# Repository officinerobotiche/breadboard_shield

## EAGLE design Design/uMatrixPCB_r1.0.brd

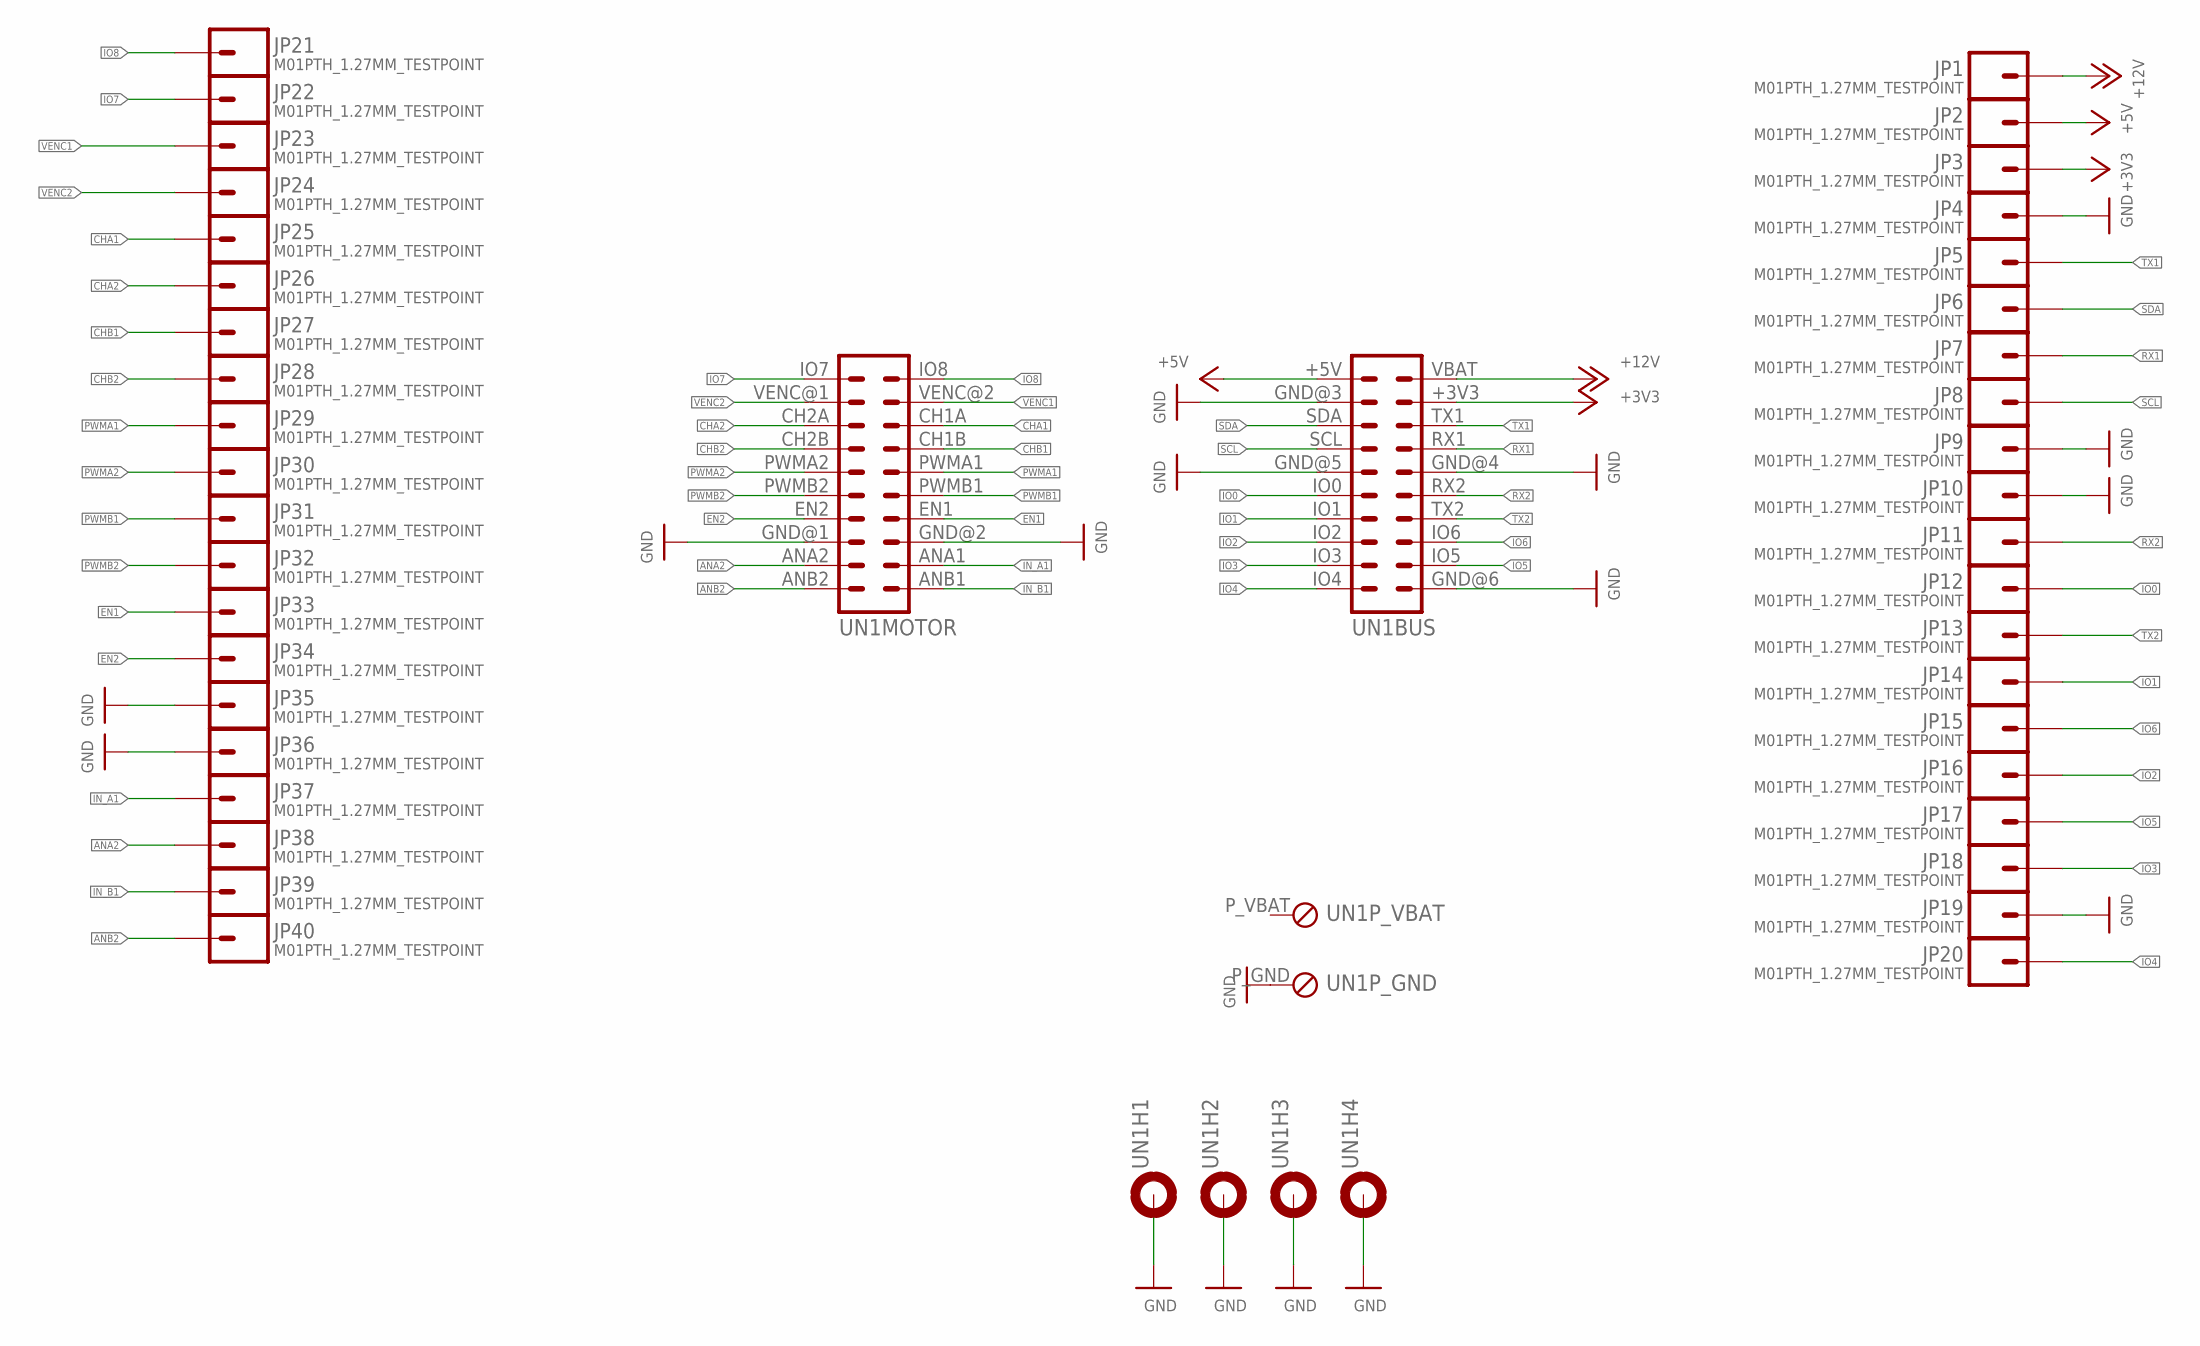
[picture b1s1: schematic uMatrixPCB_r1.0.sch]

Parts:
JP1, JP2, JP3, JP4, JP5, JP6, JP7, JP8, JP9, JP10, JP11, JP12, JP13, JP14, JP15, JP16, JP17, JP18, JP19, JP20, JP21, JP22, JP23, JP24, JP25, JP26, JP27, JP28, JP29, JP30, JP31, JP32, JP33, JP34, JP35, JP36, JP37, JP38, JP39, JP40: M01PTH_1.27MM_TESTPOINT; 1X0.127_TESTPOINT
UN1: UNAV; UNAV_BOARD

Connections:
+3V3: JP3.1, UN1.+3V3 (3)
+5V: JP2.1, UN1.+5V (2)
+12V: JP1.1, UN1.VBAT (1)
ANA2: JP38.1, UN1.ANA2 (18)
ANB2: JP40.1, UN1.ANB2 (20)
CHA1: JP25.1, UN1.CH1A (5)
CHA2: JP26.1, UN1.CH2A (6)
CHB1: JP27.1, UN1.CH1B (7)
CHB2: JP28.1, UN1.CH2B (8)
EN1: JP33.1, UN1.EN1 (13)
EN2: JP34.1, UN1.EN2 (14)
GND: JP4.1, JP9.1, JP10.1, JP19.1, JP35.1, JP36.1, UN1.GND@1 (16), UN1.GND@2 (15), UN1.GND@3 (4), UN1.GND@4 (9), UN1.GND@5 (10), UN1.GND@6 (19), UN1.H1 (MOUNT), UN1.H2 (MOUNT), UN1.H3 (MOUNT), UN1.H4 (MOUNT), UN1.P_GND (1)
IN_A1: JP37.1, UN1.ANA1 (17)
IN_B1: JP39.1, UN1.ANB1 (19)
IO0: JP12.1, UN1.IO0 (12)
IO1: JP14.1, UN1.IO1 (14)
IO2: JP16.1, UN1.IO2 (16)
IO3: JP18.1, UN1.IO3 (18)
IO4: JP20.1, UN1.IO4 (20)
IO5: JP17.1, UN1.IO5 (17)
IO6: JP15.1, UN1.IO6 (15)
IO7: JP22.1, UN1.IO7 (2)
IO8: JP21.1, UN1.IO8 (1)
PWMA1: JP29.1, UN1.PWMA1 (9)
PWMA2: JP30.1, UN1.PWMA2 (10)
PWMB1: JP31.1, UN1.PWMB1 (11)
PWMB2: JP32.1, UN1.PWMB2 (12)
RX1: JP7.1, UN1.RX1 (7)
RX2: JP11.1, UN1.RX2 (11)
SCL: JP8.1, UN1.SCL (8)
SDA: JP6.1, UN1.SDA (6)
TX1: JP5.1, UN1.TX1 (5)
TX2: JP13.1, UN1.TX2 (13)
VENC1: JP23.1, UN1.VENC@2 (3)
VENC2: JP24.1, UN1.VENC@1 (4)

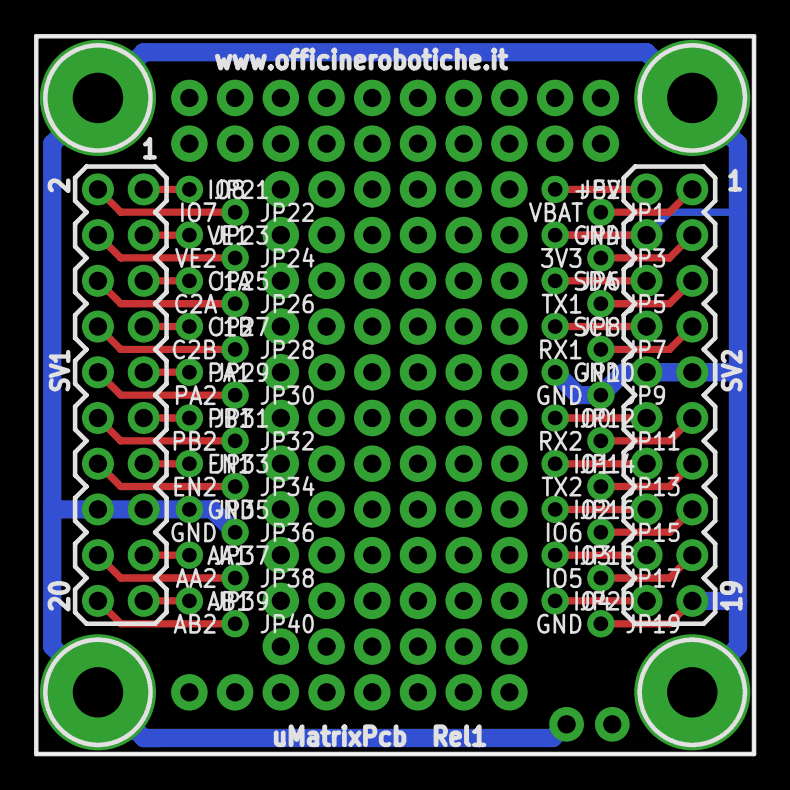
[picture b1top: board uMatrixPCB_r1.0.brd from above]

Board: 2 copper layers, 39.9 x 39.9 mm, 41 parts (0 on the bottom side), 35 nets.

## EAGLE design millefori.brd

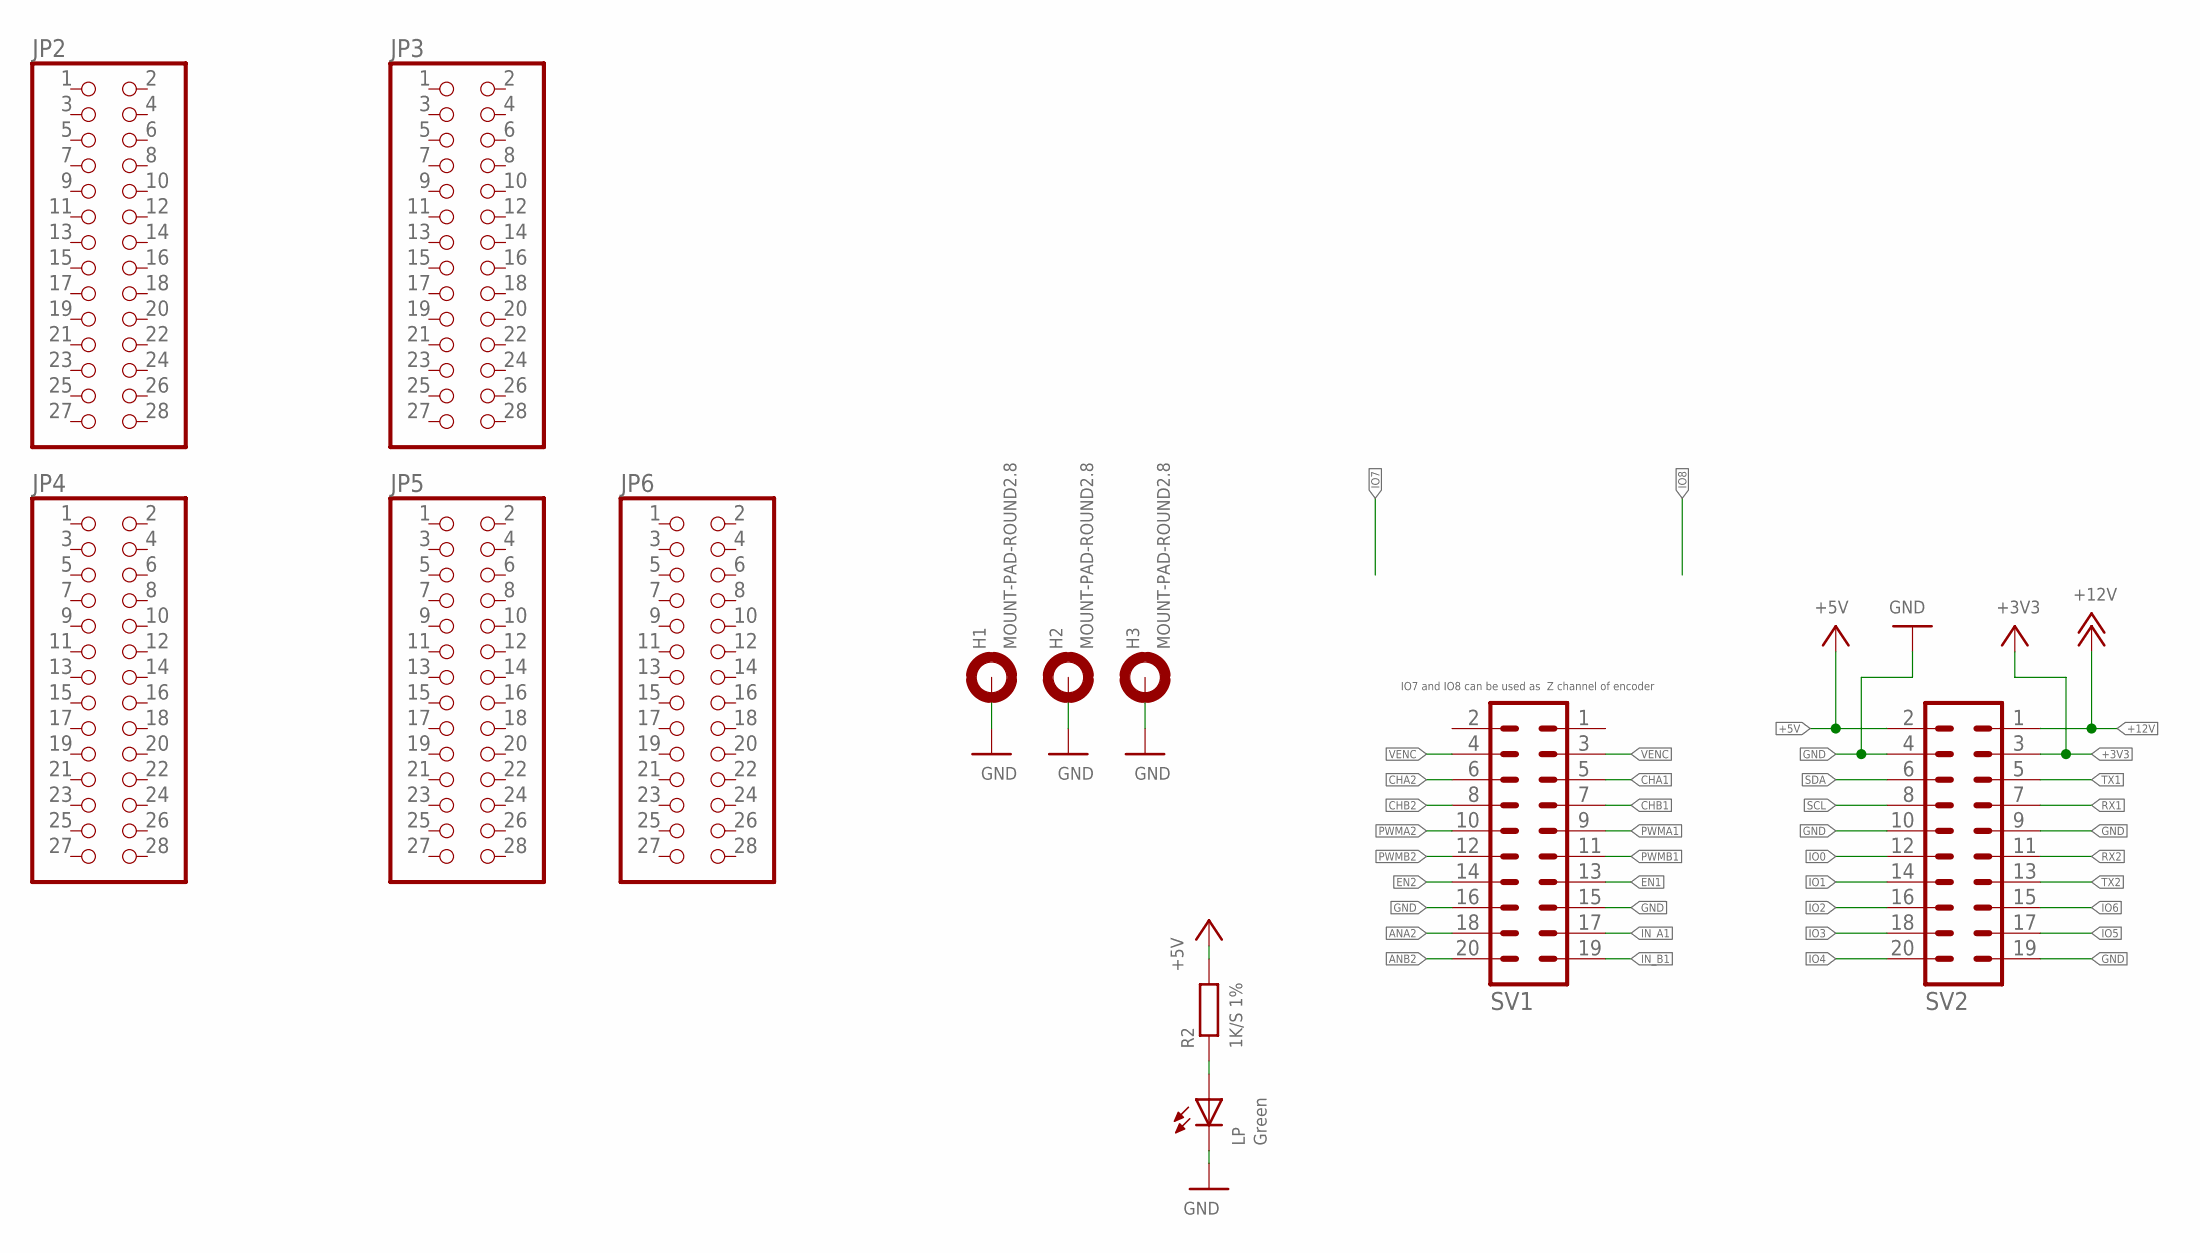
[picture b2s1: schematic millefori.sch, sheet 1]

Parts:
H1, H2, H3: MOUNT-PAD-ROUND2.8; 2,8-PAD
JP2, JP3, JP4, JP5, JP6: PINHD-2X14; 2X14
LP: Green; CHIPLED_0805
R2: 1K/S 1%; R0603
SV1, SV2: MA10-2

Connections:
+3V3: SV2.3
+5V: R2.2, SV2.2
+12V: SV2.1
ANA2: SV1.18
ANB2: SV1.20
CHA1: SV1.5
CHA2: SV1.6
CHB1: SV1.7
CHB2: SV1.8
EN1: SV1.13
EN2: SV1.14
GND: H1.B2,8, H2.B2,8, H3.B2,8, LP.C, SV1.15, SV1.16, SV2.4, SV2.9, SV2.10, SV2.19
IN_A1: SV1.17
IN_B1: SV1.19
IO0: SV2.12
IO1: SV2.14
IO2: SV2.16
IO3: SV2.18
IO4: SV2.20
IO5: SV2.17
IO6: SV2.15
unnamed: LP.A, R2.1
PWMA1: SV1.9
PWMA2: SV1.10
PWMB1: SV1.11
PWMB2: SV1.12
RX1: SV2.7
RX2: SV2.11
SCL: SV2.8
SDA: SV2.6
TX1: SV2.5
TX2: SV2.13
VENC: SV1.3, SV1.4

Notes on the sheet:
IO7 and IO8 can be used as Z channel of encoder

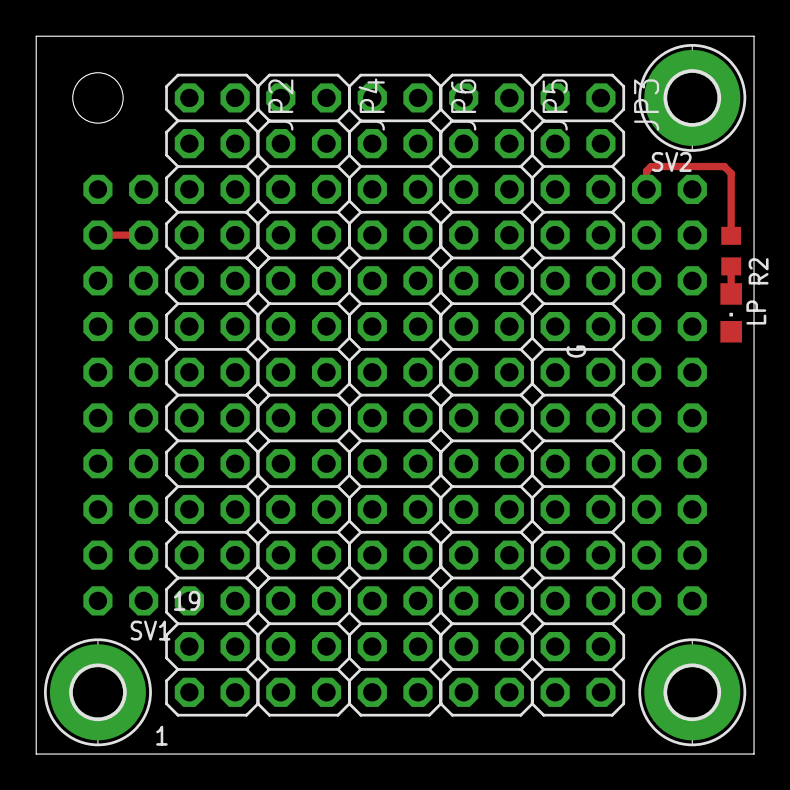
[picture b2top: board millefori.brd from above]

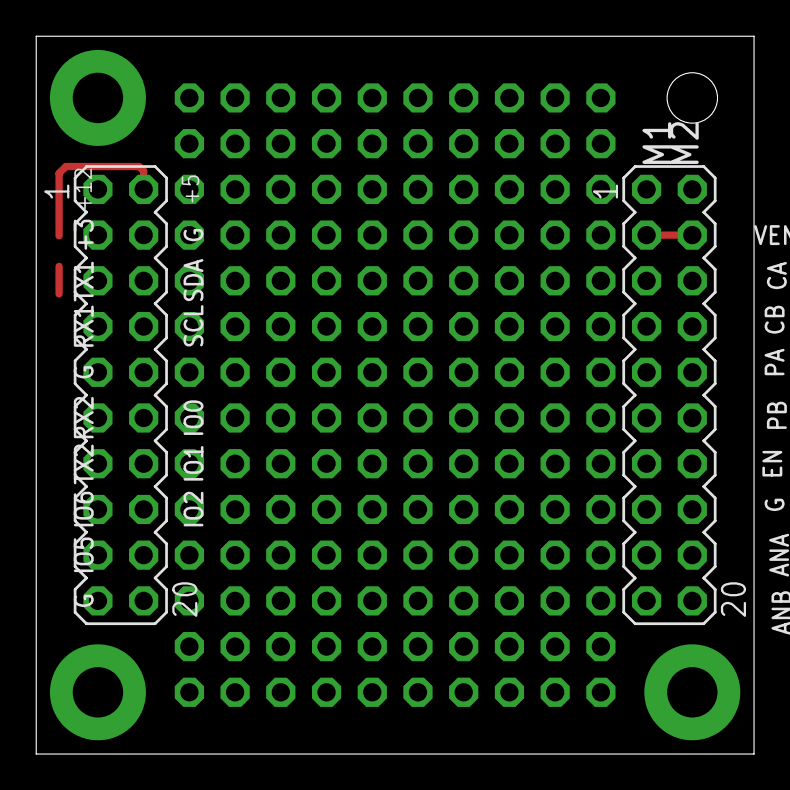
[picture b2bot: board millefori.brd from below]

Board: 2 copper layers, 39.9 x 39.9 mm, 12 parts (2 on the bottom side), 4 nets.

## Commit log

2015-01-23 First version
2015-01-23 gitignore
2015-01-24 Final Release of Matrix ProtoBoard V1
2015-01-26 Final revision sended in production.
